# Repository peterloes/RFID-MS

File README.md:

# RFID Management System RFID-MS
 
Authors: Loës P., Skripsky P., Kempenaers B. (2019) 

### Platform for animal observation 

An efficient system to monitor animal behaviour in wildlife
as well as in laboratory settings.

-	Compatible with different RFID systems and triggers
-	Low power consumption and specific data collection lead to long lasting collection periods
-	Applicable world-wide due to its compatibility with different types of radio clock receivers 
-	High observation quality through low disturbance of the animals

- Time Synchronization with atomic clock once a day to ensure optimal data quality
- Current Control twice a day
- Forecast for Battery-Change implemented
- Energy Bypass so that Date and Time are maintained even when changing battery
- Hyperterminal Output to get real-time data to the computer/laptop
- Low-Power Device:sleep: 40µA@12V awake: 12mA@12V

SmartNestBox Application:

https://github.com/peterloes/RFID-MS/blob/master/Getting_Started_Tutorial/1_poster_overview_2.pdf

Raw data on SD Card:

https://github.com/peterloes/RFID-MS/blob/master/Getting_Started_Tutorial/6_rawdata_BOX0001.TXT

Optional components:

https://github.com/peterloes/Light_Barrier

https://github.com/peterloes/Booter_RFID-MS_MOMO_TAMDL

https://github.com/peterloes/Clock_receiver_RFID-MS_MOMO_TAMDL

Manufacture:

https://github.com/peterloes/RFID-MS/blob/master/Getting_Started_Tutorial/5_Supplier.txt

C is the Greenest Programming Language

To achieve its power and energy-efficiency features, EFM32 products utilize ultralow active and idle power,
fast wakeup and processing times, and most important, the ability to intelligently interact with peripherals
and sensors autonomously without waking up the CPU and consuming more power.

[\[paper\]](https://www.sciencedirect.com/science/article/pii/S0003347223000258?via%3Dihub)
Data on the Start and End of Activity.
All 277 nestboxes were equipped with a monitoring system that
automatically recorded each nestbox visit of a PIT-tagged individual.

https://www.mpg.de/14346664/0113-verh-060830-first-come-first-bred

https://www.mpg.de/14345523/0113-verh-060830-wer-zuerst-kommt-bruetet-zuerst

EXTENSION:

Smart nest-box with long range RFID reader and external light barrier.

https://github.com/peterloes/RFID-MS/blob/master/Getting_Started_Tutorial/3_SNB_LR_LB.jpg

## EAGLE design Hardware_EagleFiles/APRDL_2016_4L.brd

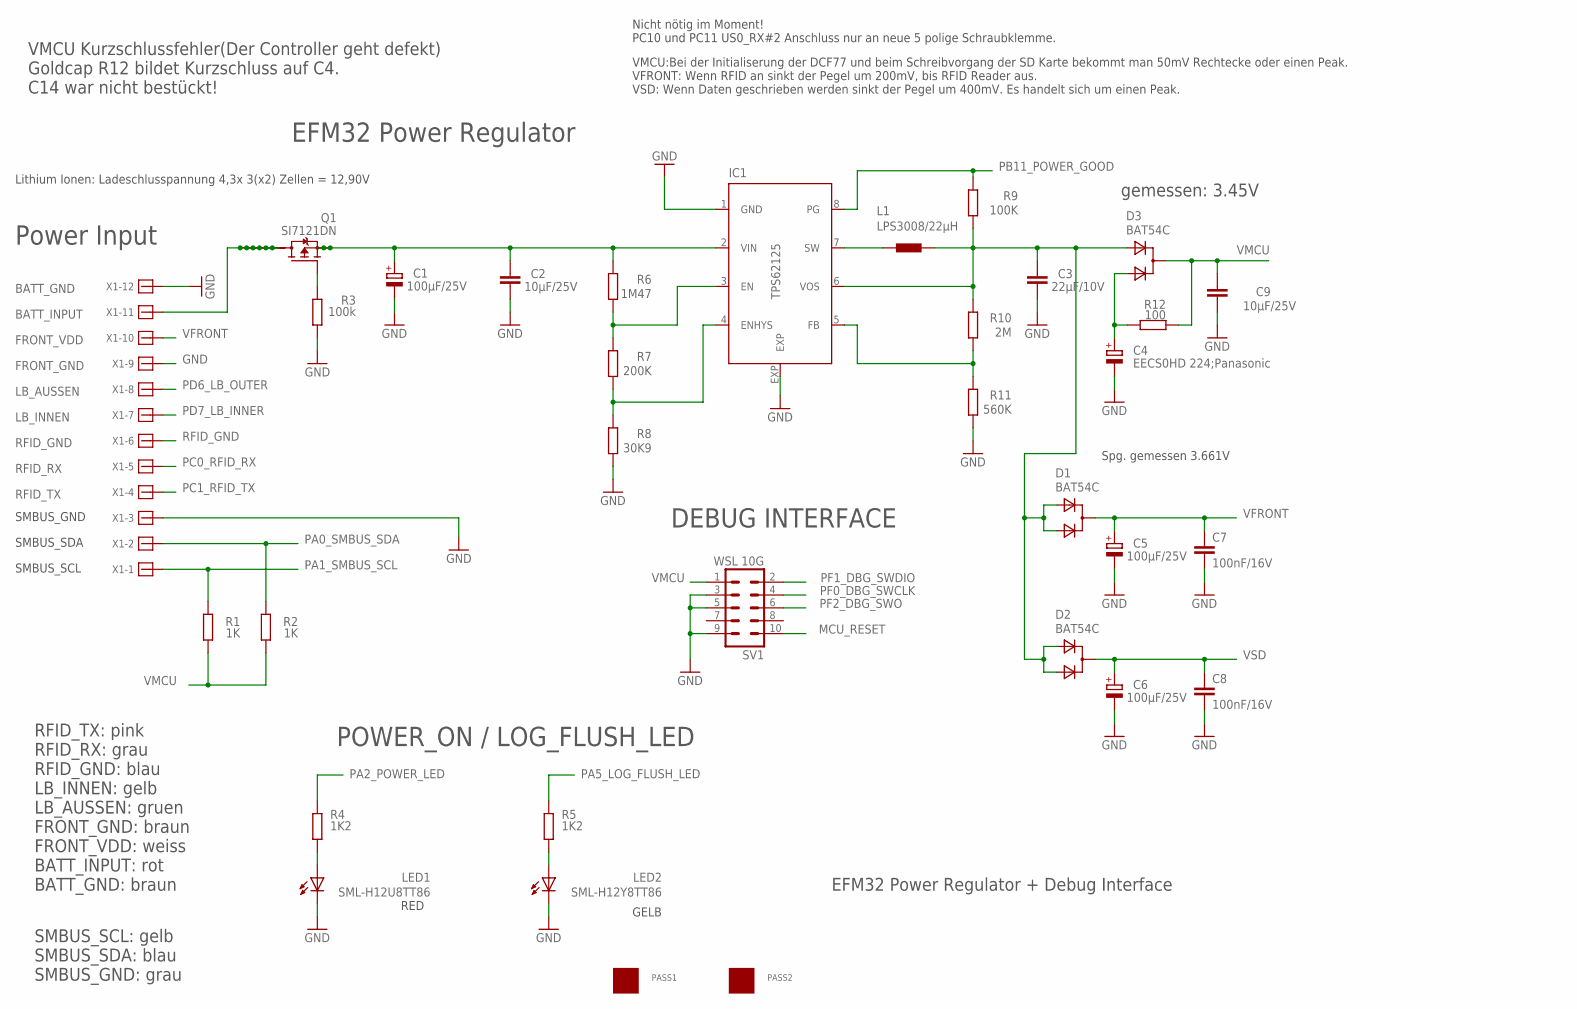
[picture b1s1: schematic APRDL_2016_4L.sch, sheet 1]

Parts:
C1, C5, C6: 100µF/25V; PANASONIC_E
C2, C9: 10µF/25V; C1206
C3: 22µF/10V; C1206
C4: EECS0HD 224;Panasonic; GOLDCAPSPK-V
C7, C8: 100nF/16V; C0805
D1, D2, D3: BAT54C; SOT-23@1
IC1: TPS62125; DSG_PWSO-N8_EXP
L1: LPS3008/22µH; LPS3008
LED1: SML-H12U8TT86; CHIPLED_0805
LED2: SML-H12Y8TT86; CHIPLED_0805
PASS1, PASS2: ROUND_1MM1.5; ROUND2_1.5MM
Q1: SI7121DN; TRANSISTOR-FET_1212-8S
R1, R2: 1K; R0805
R3: 100k; R0805
R4, R5: 1K2; R0805
R6: 1M47; R0805
R7: 200K; R0805
R8: 30K9; R0805
R9: 100K; R0805
R10: 2M; R0805
R11: 560K; R0805
R12: 100; R0805
SV1: WSL 10G; ML10
X1: 1803523

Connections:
BATT_INPUT: Q1.5 (D), Q1.6 (D), Q1.7 (D), Q1.8 (D), Q1.9 (D), Q1.10 (D), Q1.11 (D), X1.11
GND: C1.-, C2.2, C3.2, C4.-, C5.-, C6.-, C7.2, C8.2, C9.1, IC1.1 (GND), IC1.EXP, LED1.C, LED2.C, R3.1, R8.1, R11.1, SV1.3, SV1.5, SV1.9, X1.3, X1.9, X1.12; also elsewhere on the board
MCU_RESET: SV1.10; also elsewhere on the board
unnamed: IC1.3 (EN), R6.1, R7.2
unnamed: IC1.4 (ENHYS), R7.1, R8.2
unnamed: IC1.7 (SW), L1.1
unnamed: C1.+, C2.1, IC1.2 (VIN), Q1.1 (S), Q1.2 (S), Q1.3 (S), R6.2
unnamed: LED2.A, R5.2
unnamed: IC1.5 (FB), R10.1, R11.2
unnamed: Q1.4 (G), R3.2
unnamed: C4.+, D3.2 (A1), R12.2
unnamed: LED1.A, R4.2
PA0_SMBUS_SDA: R2.2, X1.2; also elsewhere on the board
PA1_SMBUS_SCL: R1.2, X1.1; also elsewhere on the board
PA2_POWER_LED: R4.1; also elsewhere on the board
PA5_LOG_FLUSH_LED: R5.1; also elsewhere on the board
PB11_POWER_GOOD: IC1.8 (PG), R9.2; also elsewhere on the board
PC0_RFID_RX: X1.5; also elsewhere on the board
PC1_RFID_TX: X1.4; also elsewhere on the board
PD6_LB_OUTER: X1.8; also elsewhere on the board
PD7_LB_INNER: X1.7; also elsewhere on the board
PF0_DBG_SWCLK: SV1.4; also elsewhere on the board
PF1_DBG_SWDIO: SV1.2; also elsewhere on the board
PF2_DBG_SWO: SV1.6; also elsewhere on the board
RFID_GND: X1.6; also elsewhere on the board
V1: C3.1, D1.2 (A1), D1.3 (A2), D2.2 (A1), D2.3 (A2), D3.3 (A2), IC1.6 (VOS), L1.2, R9.1, R10.2
VFRONT: C5.+, C7.1, D1.1 (C), X1.10
VMCU: C9.2, D3.1 (C), R1.1, R2.1, R12.1, SV1.1; also elsewhere on the board
VSD: C6.+, C8.1, D2.1 (C); also elsewhere on the board

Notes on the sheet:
BATT_GND
Lithium Ionen: Ladeschlusspannung 4,3x 3(x2) Zellen = 12,90V
BATT_INPUT
EFM32 Power Regulator + Debug Interface
Power Input
Spg. gemessen 3.661V
LB_AUSSEN
LB_INNEN
RFID_GND
SMBUS_SCL
SMBUS_SDA
SMBUS_GND
EFM32 Power Regulator
RFID_RX
RFID_TX
DEBUG INTERFACE
POWER_ON / LOG_FLUSH_LED
FRONT_VDD
FRONT_GND
GELB
RED
gemessen: 3.45V
RFID_TX: pink RFID_RX: grau RFID_GND: blau LB_INNEN: gelb LB_AUSSEN: gruen FRONT_GND: braun FRONT_VDD: weiss BATT_INPUT: rot BATT_GND: braun
SMBUS_SCL: gelb SMBUS_SDA: blau SMBUS_GND: grau
Nicht nötig im Moment! PC10 und PC11 US0_RX#2 Anschluss nur an neue 5 polige Schraubklemme.
VMCU:Bei der Initialiserung der DCF77 und beim Schreibvorgang der SD Karte bekommt man 50mV Rechtecke oder einen Peak. VFRONT: Wenn RFID an sinkt der Pegel um 200mV, bis RFID Reader aus. VSD: Wenn Daten geschrieben werden sinkt der Pegel um 400mV. Es handelt sich um einen Peak.
VMCU Kurzschlussfehler(Der Controller geht defekt) Goldcap R12 bildet Kurzschluss auf C4. C14 war nicht bestückt!

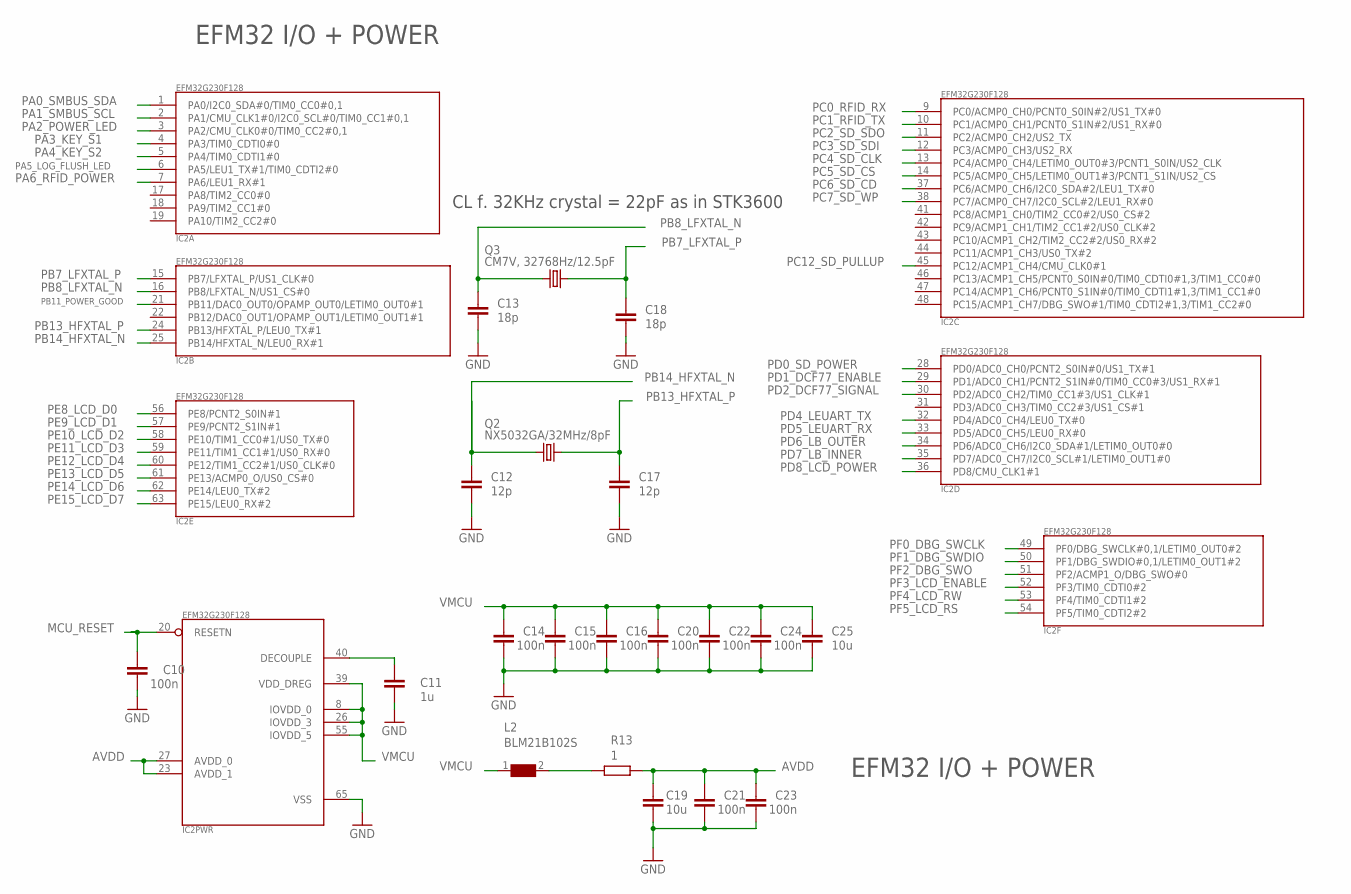
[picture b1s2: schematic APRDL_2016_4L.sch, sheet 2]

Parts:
C10, C14, C15, C16, C20, C21, C22, C23, C24: 100n; C0805
C11: 1u; C0805
C12, C17: 12p; C0805
C13, C18: 18p; C0805
C19, C25: 10u; C0805
IC2: EFM32G230F128; QFN64
L2: BLM21B102S; 0805
Q2: NX5032GA/32MHz/8pF; CRYSTAL2P5.0X3.2
Q3: CM7V, 32768Hz/12.5pF; CRYSTAL2P3.2X1.5
R13: 1; R0805

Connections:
AVDD: C19.2, C21.2, C23.2, IC2.23 (AVDD_1), IC2.27 (AVDD_0), R13.2
GND: C10.1, C11.1, C12.1, C13.1, C14.1, C15.1, C16.1, C17.1, C18.1, C19.1, C20.1, C21.1, C22.1, C23.1, C24.1, C25.1, IC2.65 (VSS); also elsewhere on the board
MCU_RESET: C10.2, IC2.20 (RESETN); also elsewhere on the board
unnamed: L2.2, R13.1
unnamed: C11.2, IC2.40 (DECOUPLE)
PA0_SMBUS_SDA: IC2.1 (PA0/I2C0_SDA#0/TIM0_CC0#0,1); also elsewhere on the board
PA1_SMBUS_SCL: IC2.2 (PA1/CMU_CLK1#0/I2C0_SCL#0/TIM0_CC1#0,1); also elsewhere on the board
PA2_POWER_LED: IC2.3 (PA2/CMU_CLK0#0/TIM0_CC2#0,1); also elsewhere on the board
PA3_KEY_S1: IC2.4 (PA3/TIM0_CDTI0#0); also elsewhere on the board
PA4_KEY_S2: IC2.5 (PA4/TIM0_CDTI1#0); also elsewhere on the board
PA5_LOG_FLUSH_LED: IC2.6 (PA5/LEU1_TX#1/TIM0_CDTI2#0); also elsewhere on the board
PA6_RFID_POWER: IC2.7 (PA6/LEU1_RX#1); also elsewhere on the board
PB7_LFXTAL_P: C18.2, IC2.15 (PB7/LFXTAL_P/US1_CLK#0), Q3.2
PB8_LFXTAL_N: C13.2, IC2.16 (PB8/LFXTAL_N/US1_CS#0), Q3.1
PB11_POWER_GOOD: IC2.21 (PB11/DAC0_OUT0/OPAMP_OUT0/LETIM0_OUT0#1); also elsewhere on the board
PB13_HFXTAL_P: C17.2, IC2.24 (PB13/HFXTAL_P/LEU0_TX#1), Q2.2
PB14_HFXTAL_N: C12.2, IC2.25 (PB14/HFXTAL_N/LEU0_RX#1), Q2.1
PC0_RFID_RX: IC2.9 (PC0/ACMP0_CH0/PCNT0_S0IN#2/US1_TX#0); also elsewhere on the board
PC1_RFID_TX: IC2.10 (PC1/ACMP0_CH1/PCNT0_S1IN#2/US1_RX#0); also elsewhere on the board
PC2_SD_SDO: IC2.11 (PC2/ACMP0_CH2/US2_TX); also elsewhere on the board
PC3_SD_SDI: IC2.12 (PC3/ACMP0_CH3/US2_RX); also elsewhere on the board
PC4_SD_CLK: IC2.13 (PC4/ACMP0_CH4/LETIM0_OUT0#3/PCNT1_S0IN/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); also elsewhere on the board
PC5_SD_CS: IC2.14 (PC5/ACMP0_CH5/LETIM0_OUT1#3/PCNT1_S1IN/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); also elsewhere on the board
PC6_SD_CD: IC2.37 (PC6/ACMP0_CH6/I2C0_SDA#2/LEU1_TX#0); also elsewhere on the board
PC7_SD_WP: IC2.38 (PC7/ACMP0_CH7/I2C0_SCL#2/LEU1_RX#0); also elsewhere on the board
PC12_SD_PULLUP: IC2.45 (PC12/ACMP1_CH4/CMU_CLK0#1); also elsewhere on the board
PD0_SD_POWER: IC2.28 (PD0/ADC0_CH0/PCNT2_S0IN#0/US1_TX#1); also elsewhere on the board
PD1_DCF77_ENABLE: IC2.29 (PD1/ADC0_CH1/PCNT2_S1IN#0/TIM0_CC0#3/US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); also elsewhere on the board
PD2_DCF77_SIGNAL: IC2.30 (PD2/ADC0_CH2/TIM0_CC1#3/US1_CLK#1); also elsewhere on the board
PD4_LEUART_TX: IC2.32 (PD4/ADC0_CH4/LEU0_TX#0); also elsewhere on the board
PD5_LEUART_RX: IC2.33 (PD5/ADC0_CH5/LEU0_RX#0); also elsewhere on the board
PD6_LB_OUTER: IC2.34 (PD6/ADC0_CH6/I2C0_SDA#1/LETIM0_OUT0#0); also elsewhere on the board
PD7_LB_INNER: IC2.35 (PD7/ADC0_CH7/I2C0_SCL#1/LETIM0_OUT1#0); also elsewhere on the board
PD8_LCD_POWER: IC2.36 (PD8/CMU_CLK1#1); also elsewhere on the board
PE8_LCD_D0: IC2.56 (PE8/PCNT2_S0IN#1); also elsewhere on the board
PE9_LCD_D1: IC2.57 (PE9/PCNT2_S1IN#1); also elsewhere on the board
PE10_LCD_D2: IC2.58 (PE10/TIM1_CC0#1/US0_TX#0); also elsewhere on the board
PE11_LCD_D3: IC2.59 (PE11/TIM1_CC1#1/US0_RX#0); also elsewhere on the board
PE12_LCD_D4: IC2.60 (PE12/TIM1_CC2#1/US0_CLK#0); also elsewhere on the board
PE13_LCD_D5: IC2.61 (PE13/ACMP0_O/US0_CS#0); also elsewhere on the board
PE14_LCD_D6: IC2.62 (PE14/LEU0_TX#2); also elsewhere on the board
PE15_LCD_D7: IC2.63 (PE15/LEU0_RX#2); also elsewhere on the board
PF0_DBG_SWCLK: IC2.49 (PF0/DBG_SWCLK#0,1/LETIM0_OUT0#2); also elsewhere on the board
PF1_DBG_SWDIO: IC2.50 (PF1/DBG_SWDIO#0,1/LETIM0_OUT1#2); also elsewhere on the board
PF2_DBG_SWO: IC2.51 (PF2/ACMP1_O/DBG_SWO#0); also elsewhere on the board
PF3_LCD_ENABLE: IC2.52 (PF3/TIM0_CDTI0#2); also elsewhere on the board
PF4_LCD_RW: IC2.53 (PF4/TIM0_CDTI1#2); also elsewhere on the board
PF5_LCD_RS: IC2.54 (PF5/TIM0_CDTI2#2); also elsewhere on the board
VMCU: C14.2, C15.2, C16.2, C20.2, C22.2, C24.2, C25.2, IC2.8 (IOVDD_0), IC2.26 (IOVDD_3), IC2.39 (VDD_DREG), IC2.55 (IOVDD_5), L2.1; also elsewhere on the board

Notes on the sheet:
EFM32 I/O + POWER
CL f. 32KHz crystal = 22pF as in STK3600

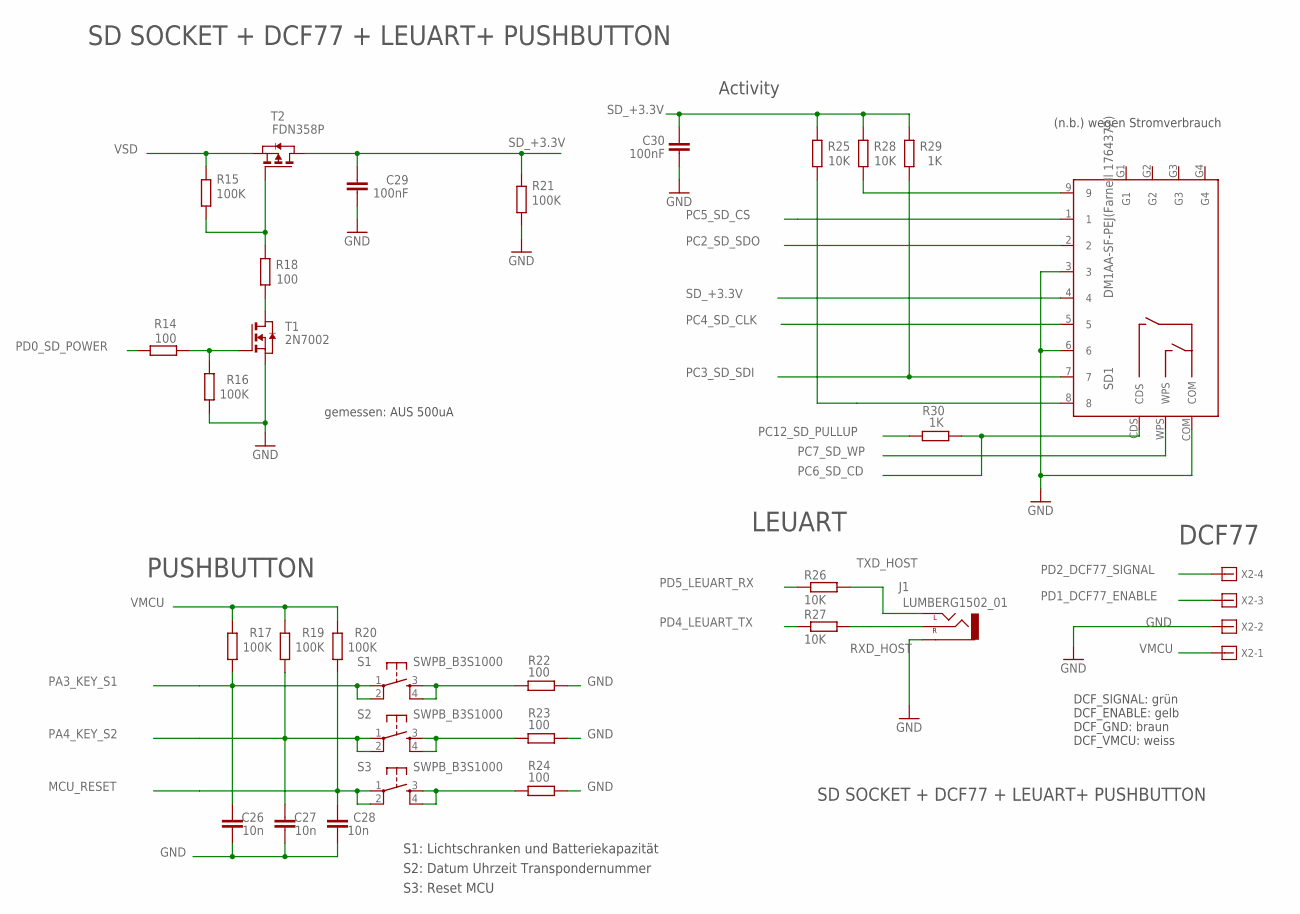
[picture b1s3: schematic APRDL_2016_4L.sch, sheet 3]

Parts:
C26, C27, C28: 10n; C0603
C29, C30: 100nF; C0603
J1: LUMBERG1502_01
R14, R18, R22, R23, R24: 100; R0805
R15, R16, R17, R19, R20, R21: 100K; R0805
R25, R26, R27, R28: 10K; R0805
R29, R30: 1K; R0805
S1, S2, S3: SWPB_B3S1000; DTSM-6
SD1: DM1AA-SF-PEJ(Farnell 1764372); DM1AA-SF-PEJ
T1: 2N7002; ZETEX_SOT-23
T2: FDN358P; ZETEX_SOT-23
X2: 1803442

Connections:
GND: C26.1, C27.1, C28.1, C29.2, C30.2, J1.P$1 (1-SLEEVE), R16.1, R21.1, R22.2, R23.2, R24.2, SD1.3, SD1.6, SD1.COM, T1.2 (S), X2.2; also elsewhere on the board
MCU_RESET: C28.2, R20.1, S3.1, S3.2; also elsewhere on the board
unnamed: R15.1, R18.2, T2.3 (G)
unnamed: R18.1, T1.1 (D)
unnamed: R14.1, R16.2, T1.3 (G)
unnamed: R28.1, SD1.9
unnamed: R25.1, SD1.8
unnamed: R22.1, S1.3, S1.4
unnamed: R23.1, S2.3, S2.4
unnamed: R24.1, S3.3, S3.4
PA3_KEY_S1: C26.2, R17.1, S1.1, S1.2; also elsewhere on the board
PA4_KEY_S2: C27.2, R19.1, S2.1, S2.2; also elsewhere on the board
PC2_SD_SDO: SD1.2; also elsewhere on the board
PC3_SD_SDI: R29.1, SD1.7; also elsewhere on the board
PC4_SD_CLK: SD1.5; also elsewhere on the board
PC5_SD_CS: SD1.1; also elsewhere on the board
PC6_SD_CD: R30.1, SD1.CDS; also elsewhere on the board
PC7_SD_WP: SD1.WPS; also elsewhere on the board
PC12_SD_PULLUP: R30.2; also elsewhere on the board
PD0_SD_POWER: R14.2; also elsewhere on the board
PD1_DCF77_ENABLE: X2.3; also elsewhere on the board
PD2_DCF77_SIGNAL: X2.4; also elsewhere on the board
PD4_LEUART_TX: R27.1; also elsewhere on the board
PD5_LEUART_RX: R26.1; also elsewhere on the board
RXD_HOST: J1.P$3 (3-RIGHT), R27.2
SD_+3.3V: C29.1, C30.1, R21.2, R25.2, R28.2, R29.2, SD1.4, T2.1 (D)
TXD_HOST: J1.P$2 (2-LEFT), R26.2
VMCU: R17.2, R19.2, R20.2, X2.1; also elsewhere on the board
VSD: R15.2, T2.2 (S); also elsewhere on the board

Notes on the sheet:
LEUART
gemessen: AUS 500uA
DCF77
Activity
PUSHBUTTON
SD SOCKET + DCF77 + LEUART+ PUSHBUTTON
S1: Lichtschranken und Batteriekapazität
S2: Datum Uhrzeit Transpondernummer
S3: Reset MCU
(n.b.) wegen Stromverbrauch
DCF_SIGNAL: grün DCF_ENABLE: gelb DCF_GND: braun DCF_VMCU: weiss

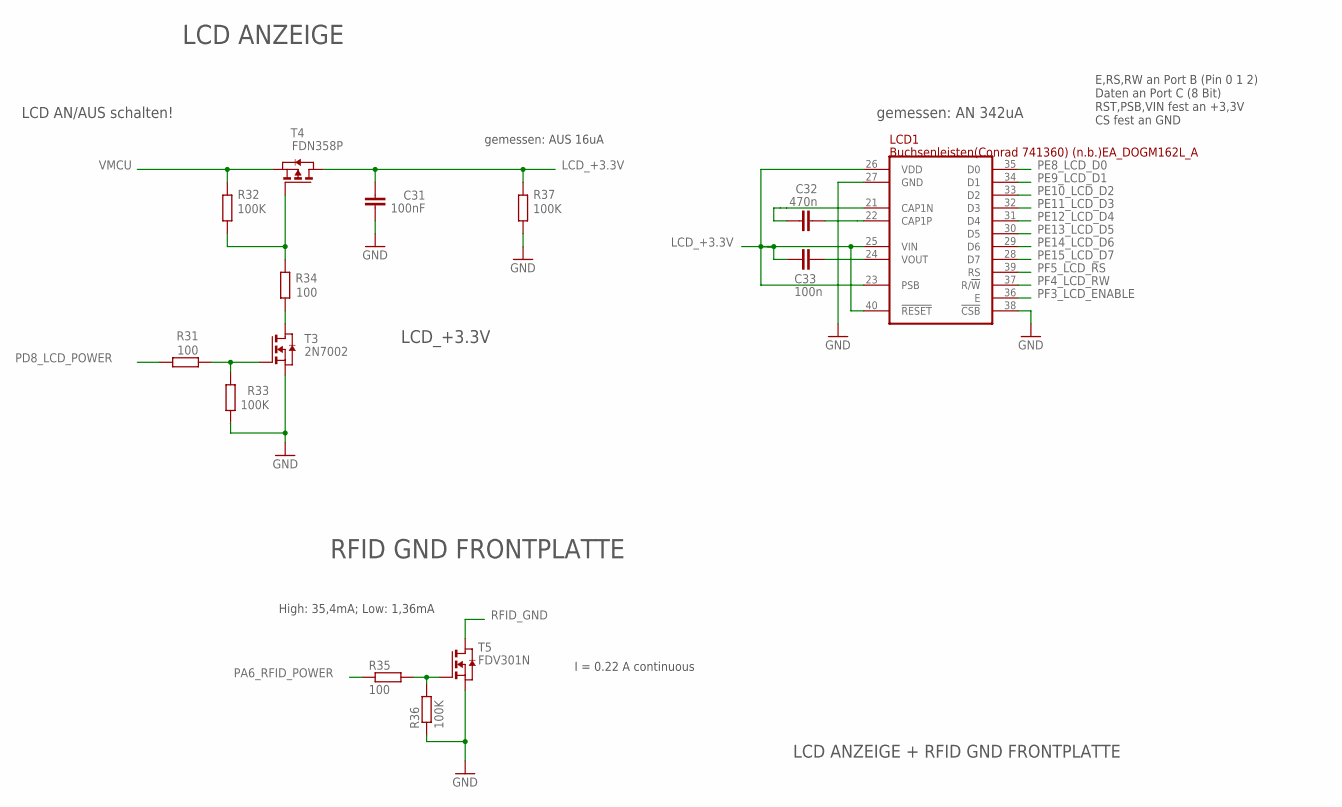
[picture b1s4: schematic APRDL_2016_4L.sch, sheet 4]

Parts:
C31: 100nF; C0603
C32: 470n; C0805
C33: 100n; C1206
LCD1: Buchsenleisten(Conrad 741360) (n.b.)EA_DOGM162L_A; EA_DOGM
R31, R34, R35: 100; R0805
R32, R33, R36, R37: 100K; R0805
T3: 2N7002; ZETEX_SOT-23
T4: FDN358P; ZETEX_SOT-23
T5: FDV301N; SOT-23

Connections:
GND: C31.2, LCD1.27 (GND), LCD1.38 (!CSB!), R33.1, R36.1, R37.1, T3.2 (S), T5.2 (S); also elsewhere on the board
LCD_+3.3V: C31.1, C33.2, LCD1.23 (PSB), LCD1.25 (VIN), LCD1.26 (VDD), LCD1.40 (!RESET!), R37.2, T4.1 (D)
unnamed: R35.2, R36.2, T5.3 (G)
unnamed: R32.1, R34.2, T4.3 (G)
unnamed: R34.1, T3.1 (D)
unnamed: R31.1, R33.2, T3.3 (G)
unnamed: C32.2, LCD1.22 (CAP1P)
unnamed: C32.1, LCD1.21 (CAP1N)
unnamed: C33.1, LCD1.24 (VOUT)
PA6_RFID_POWER: R35.1; also elsewhere on the board
PD8_LCD_POWER: R31.2; also elsewhere on the board
PE8_LCD_D0: LCD1.35 (D0); also elsewhere on the board
PE9_LCD_D1: LCD1.34 (D1); also elsewhere on the board
PE10_LCD_D2: LCD1.33 (D2); also elsewhere on the board
PE11_LCD_D3: LCD1.32 (D3); also elsewhere on the board
PE12_LCD_D4: LCD1.31 (D4); also elsewhere on the board
PE13_LCD_D5: LCD1.30 (D5); also elsewhere on the board
PE14_LCD_D6: LCD1.29 (D6); also elsewhere on the board
PE15_LCD_D7: LCD1.28 (D7); also elsewhere on the board
PF3_LCD_ENABLE: LCD1.36 (E); also elsewhere on the board
PF4_LCD_RW: LCD1.37 (R/!W!); also elsewhere on the board
PF5_LCD_RS: LCD1.39 (RS); also elsewhere on the board
RFID_GND: T5.1 (D); also elsewhere on the board
VMCU: R32.2, T4.2 (S); also elsewhere on the board

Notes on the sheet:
LCD ANZEIGE + RFID GND FRONTPLATTE
High: 35,4mA; Low: 1,36mA
RFID GND FRONTPLATTE
LCD ANZEIGE
E,RS,RW an Port B (Pin 0 1 2) Daten an Port C (8 Bit) RST,PSB,VIN fest an +3,3V CS fest an GND
gemessen: AUS 16uA
LCD_+3.3V
LCD AN/AUS schalten!
gemessen: AN 342uA
I = 0.22 A continuous

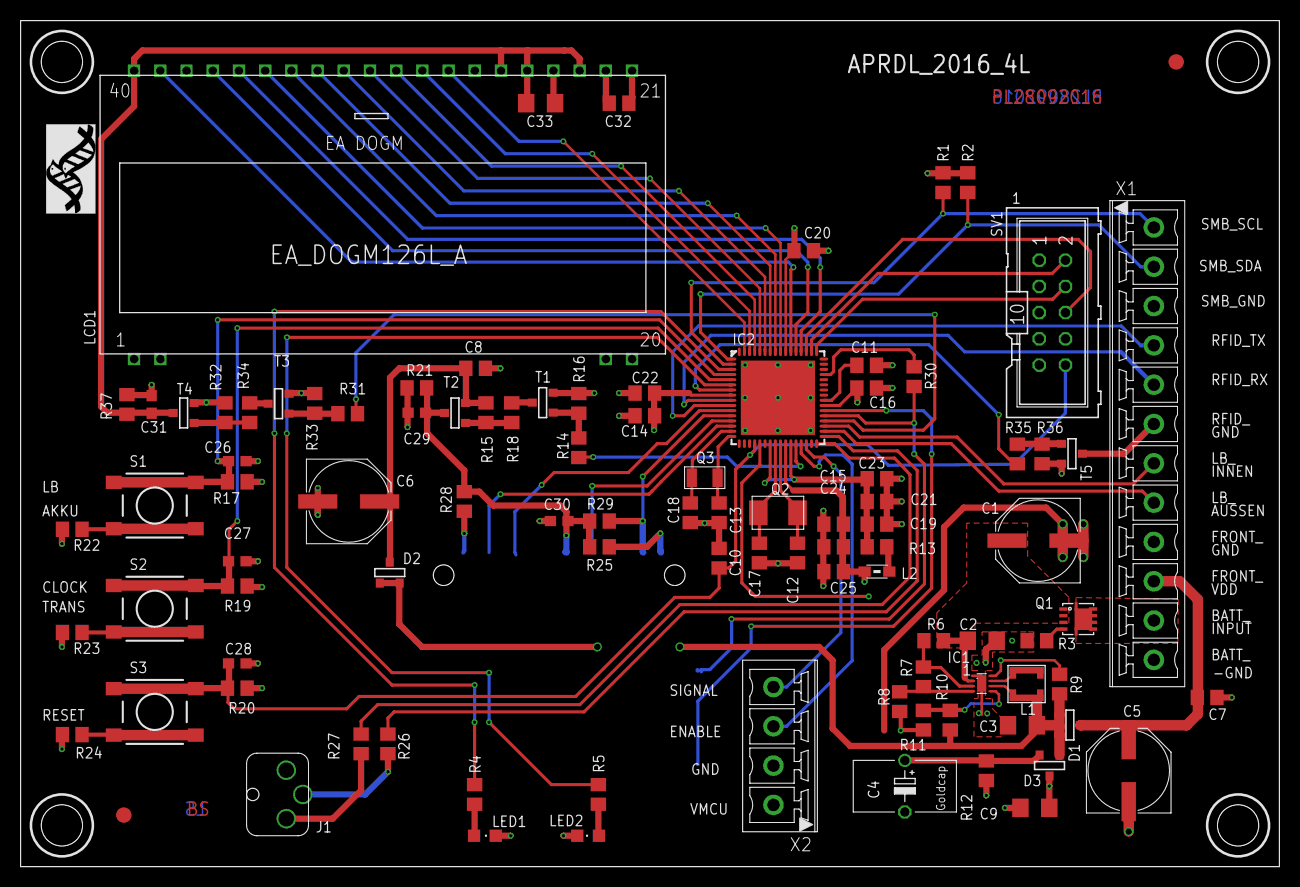
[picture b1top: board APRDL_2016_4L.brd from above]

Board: 4 copper layers, 122.0 x 82.0 mm, 99 parts (1 on the bottom side), 82 nets.

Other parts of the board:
U$2: MPIO-ICON

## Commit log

2019-09-30 Update README.md
    Lotte's feedback
2019-09-30 Update README.md
    Lotte 2
2019-09-30 Update README.md
    L3

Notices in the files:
parts and their libraries:
EnergyMicro: CC0 License
SparkFun-Aesthetics: Licensing: CC v3.0 Share-Alike You are welcome to use this library for commercial purposes.
